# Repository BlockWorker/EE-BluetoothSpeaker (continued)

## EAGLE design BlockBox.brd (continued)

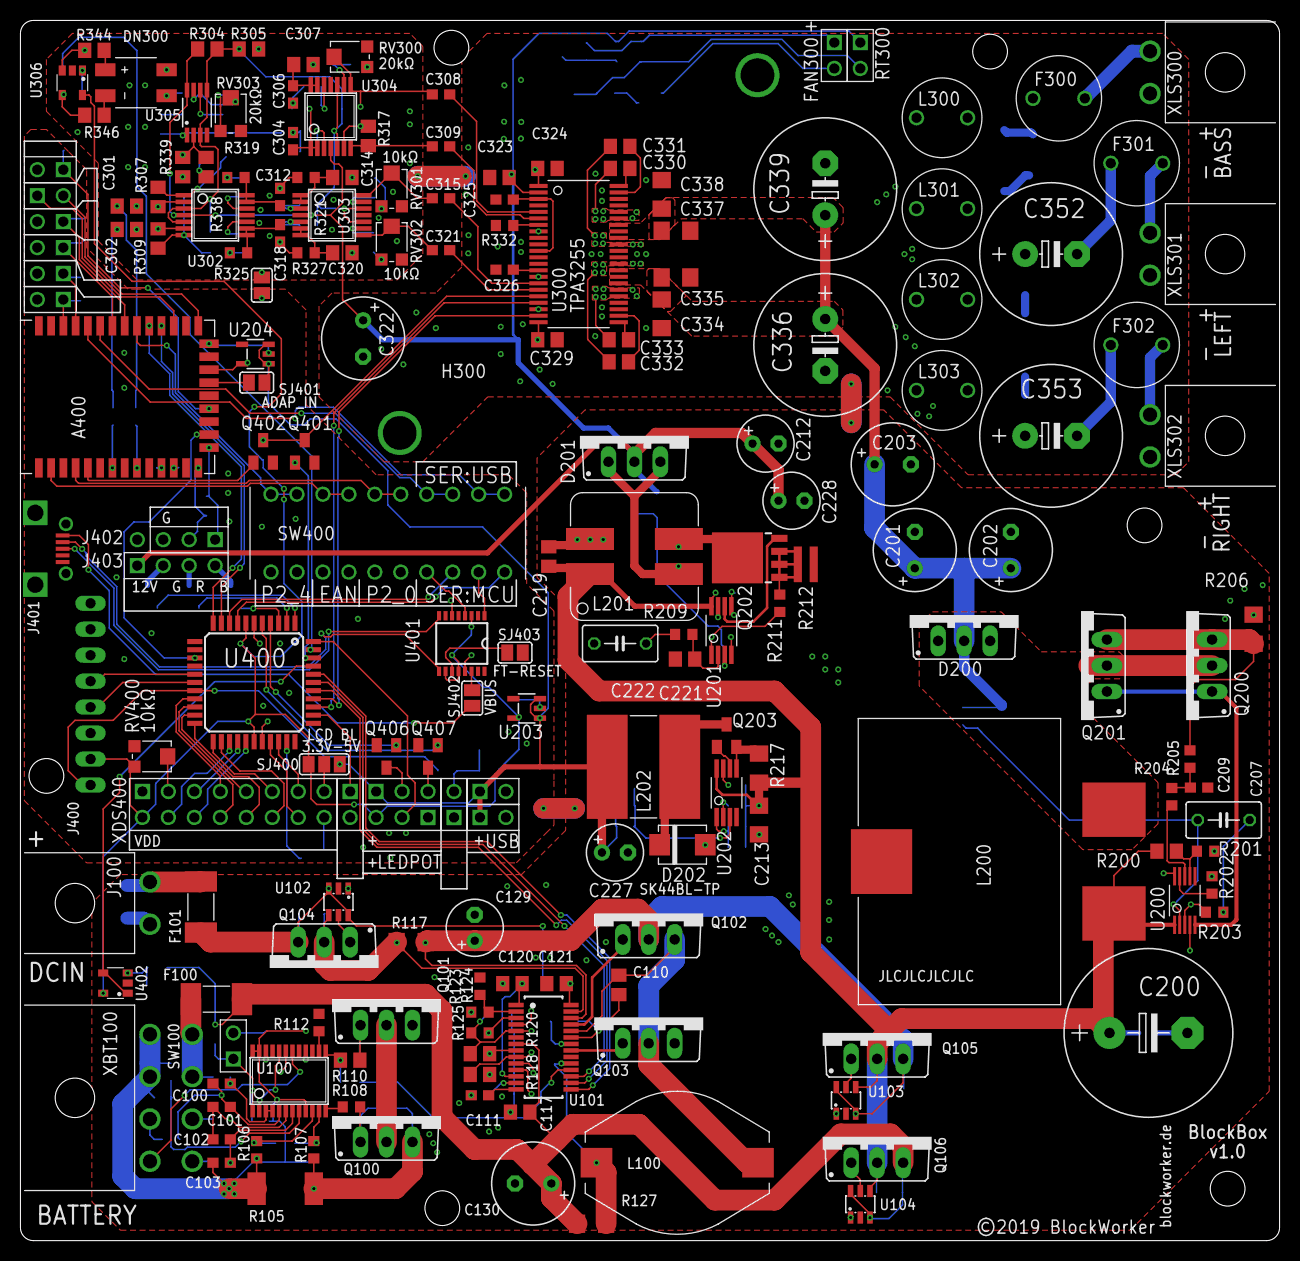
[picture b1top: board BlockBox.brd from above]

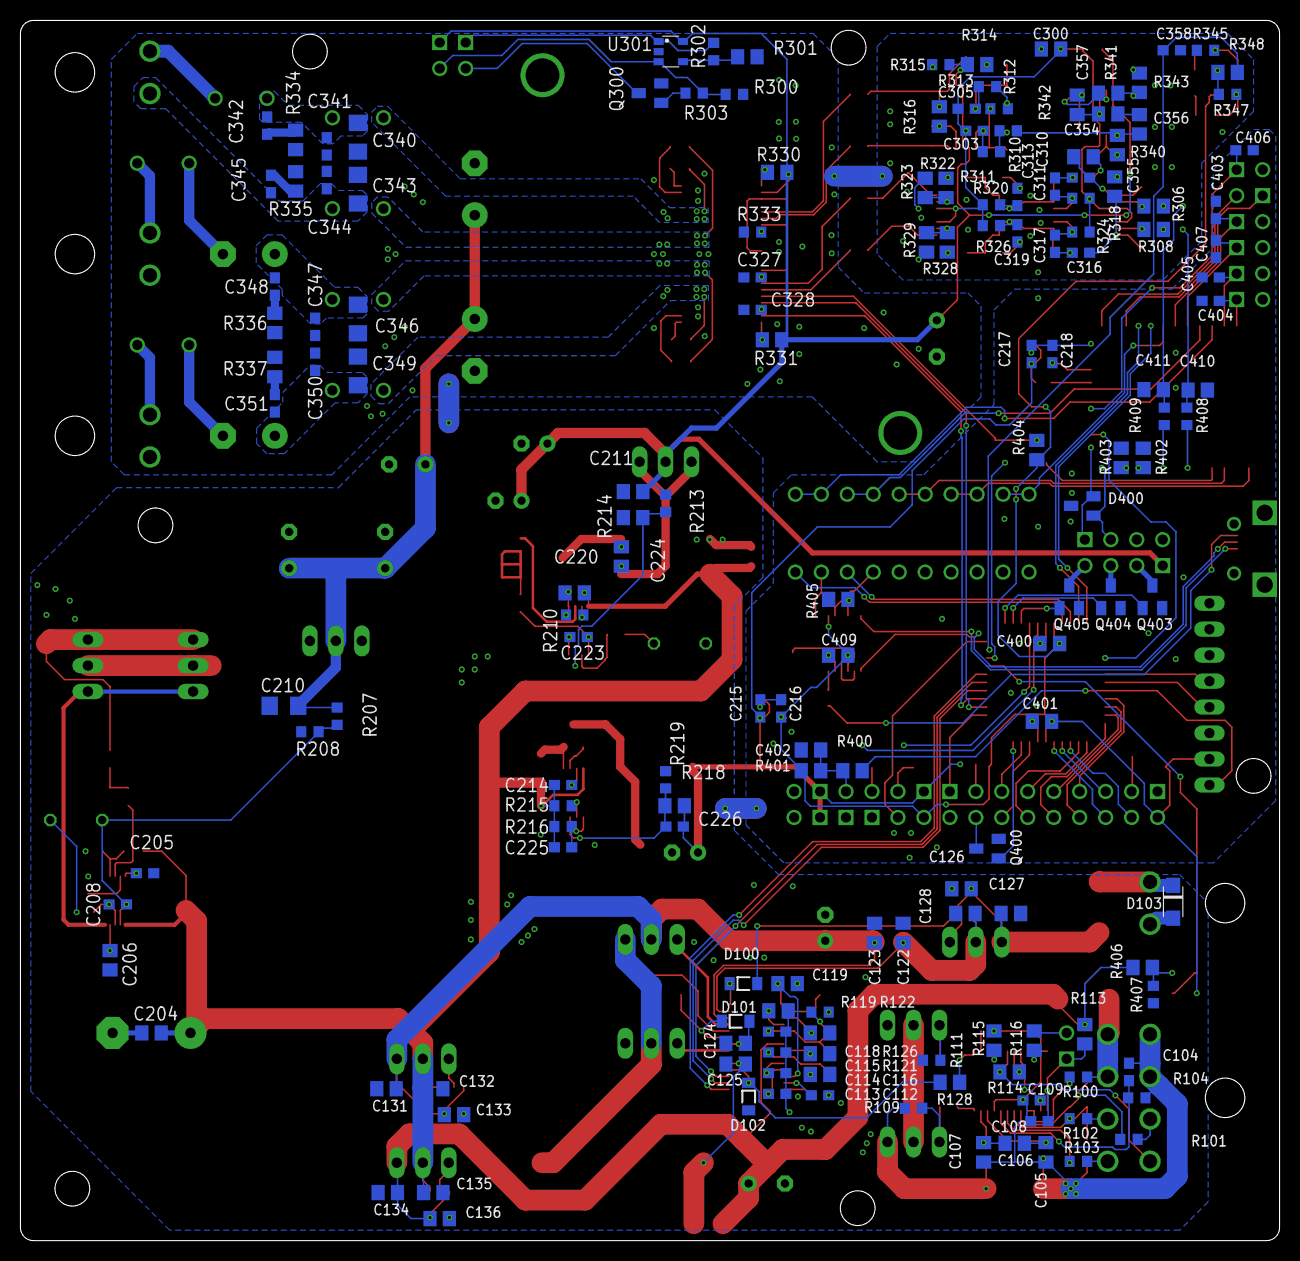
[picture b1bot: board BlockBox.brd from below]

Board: 2 copper layers, 123.2 x 119.4 mm, 344 parts (162 on the bottom side), 260 nets.

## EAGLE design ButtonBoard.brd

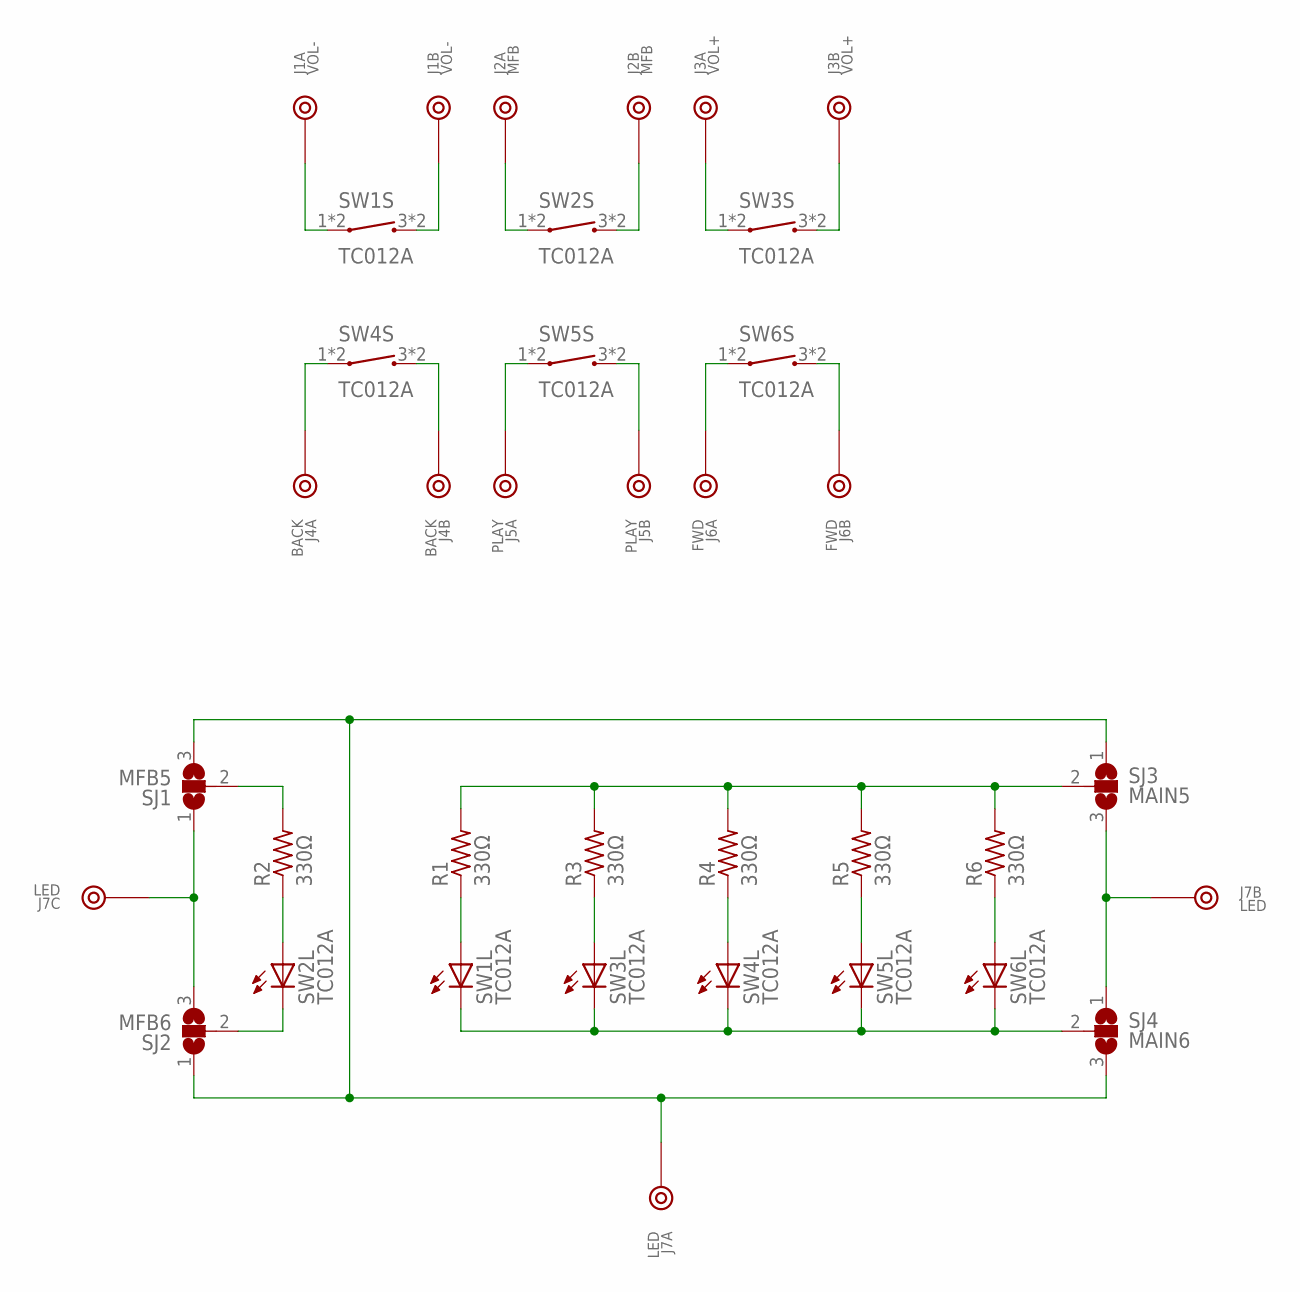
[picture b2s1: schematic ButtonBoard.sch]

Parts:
J1: VOL-; 2PIN
J2: MFB; 2PIN
J3: VOL+; 2PIN
J4: BACK; 2PIN
J5: PLAY; 2PIN
J6: FWD; 2PIN
J7: LED; 3PIN
R1, R2, R3, R4, R5, R6: 330Ω; R0805
SJ1: MFB5; SJ_2
SJ2: MFB6; SJ_2
SJ3: MAIN5; SJ_2
SJ4: MAIN6; SJ_2
SW1, SW2, SW3, SW4, SW5, SW6: TC012A

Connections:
BACK1: J4.1, SW4.1, SW4.2 (1)
BACK2: J4.2, SW4.3 (2), SW4.4 (2)
FWD1: J6.1, SW6.1, SW6.2 (1)
FWD2: J6.2, SW6.3 (2), SW6.4 (2)
LED_5V: J7.1, SJ1.3, SJ2.1, SJ3.1, SJ4.3
LED_BACK_5R: R4.1, SW4.5 (A)
LED_FWD_5R: R6.1, SW6.5 (A)
LED_MAIN_5: R1.2, R3.2, R4.2, R5.2, R6.2, SJ3.2
LED_MAIN_6: SJ4.2, SW1.6 (C), SW3.6 (C), SW4.6 (C), SW5.6 (C), SW6.6 (C)
LED_MAIN_GND: J7.2, SJ3.3, SJ4.1
LED_MFB_5: R2.2, SJ1.2
LED_MFB_5R: R2.1, SW2.5 (A)
LED_MFB_6: SJ2.2, SW2.6 (C)
LED_MFB_GND: J7.3, SJ1.1, SJ2.3
LED_PLAY_5R: R5.1, SW5.5 (A)
LED_VOL+_5R: R3.1, SW3.5 (A)
LED_VOL-_5R: R1.1, SW1.5 (A)
MFB1: J2.1, SW2.1, SW2.2 (1)
MFB2: J2.2, SW2.3 (2), SW2.4 (2)
PLAY1: J5.1, SW5.1, SW5.2 (1)
PLAY2: J5.2, SW5.3 (2), SW5.4 (2)
VOL+1: J3.1, SW3.1, SW3.2 (1)
VOL+2: J3.2, SW3.3 (2), SW3.4 (2)
VOL-1: J1.1, SW1.1, SW1.2 (1)
VOL-2: J1.2, SW1.3 (2), SW1.4 (2)

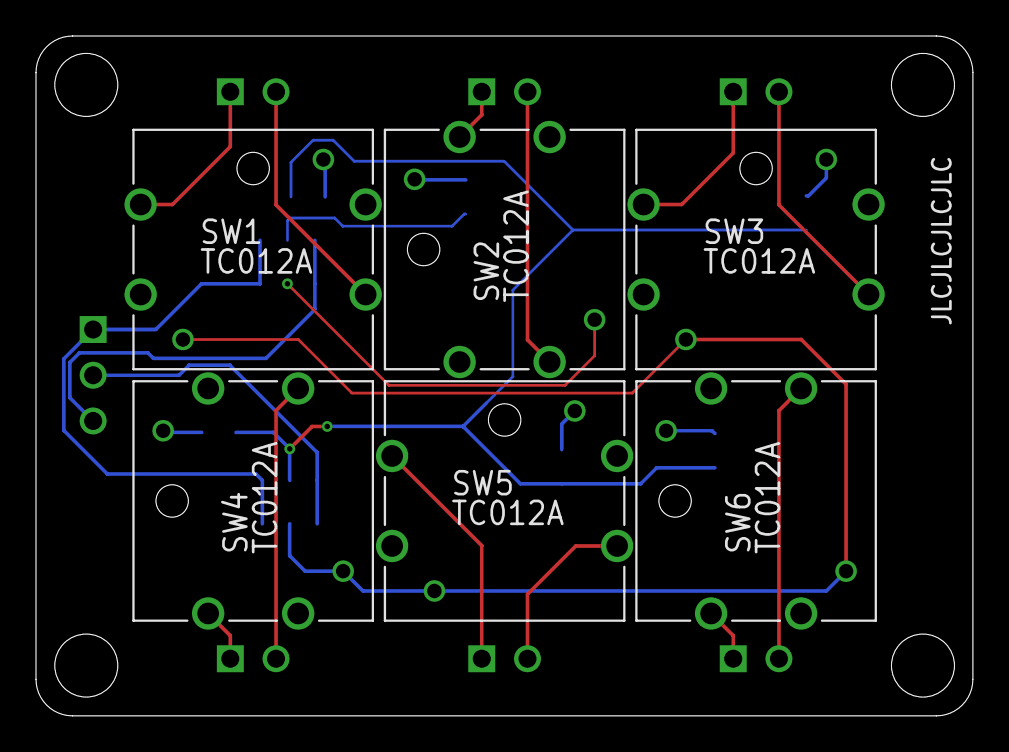
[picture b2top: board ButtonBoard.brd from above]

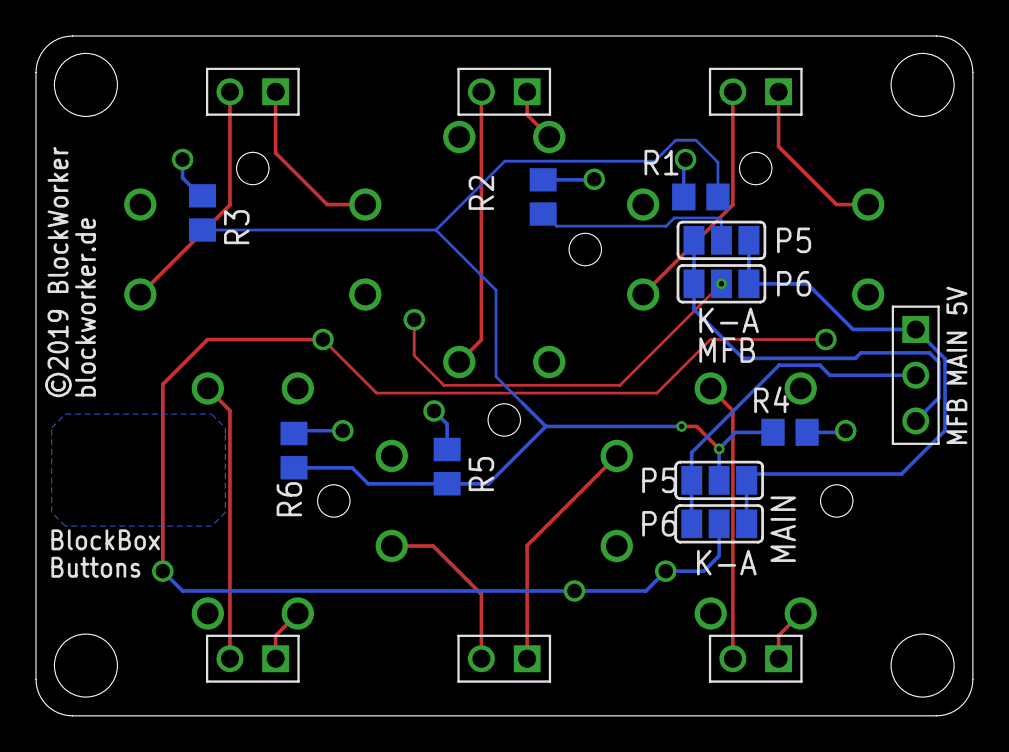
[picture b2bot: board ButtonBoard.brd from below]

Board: 2 copper layers, 52.0 x 37.8 mm, 23 parts (17 on the bottom side), 25 nets.

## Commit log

2019-08-02 Battery management & power converters done (for now).
2019-08-03 Changed 12V converter, added audio crossover & preamp stage
2019-08-05 Audio path finished, revised 5V supply
2019-08-05 Changed bass input to summing amp (L+R), added preliminary BM62 configs.
2019-08-08 Schematic mostly done, added Multisim circuit files
2019-08-09 Finished up digital section, schematic done for now.
2019-08-19 Design initially completed.
2019-08-19 Final checks and fixes applied.
2019-09-06 Added basic MCU program
2019-09-29 Minor changes to UI/DSP made during build, major MCU progress.
2019-10-09 More MCU work (mostly UART comms), small BM-UI changes.
2019-10-16 Minor changes.
2019-10-21 Changed some battery management/protection logic, made S2L more responsive (faster decay)
2020-01-08 Updates etc.
